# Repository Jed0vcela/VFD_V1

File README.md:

VFD driver for IVL1-8/13 soviet display.
Powered form 5V USB.
SPI interface that can be daisy-chained.
3,3V logic level.
Analog dimming via adjusting anode voltage.
Heater voltage adjustment implemented on board but not tested

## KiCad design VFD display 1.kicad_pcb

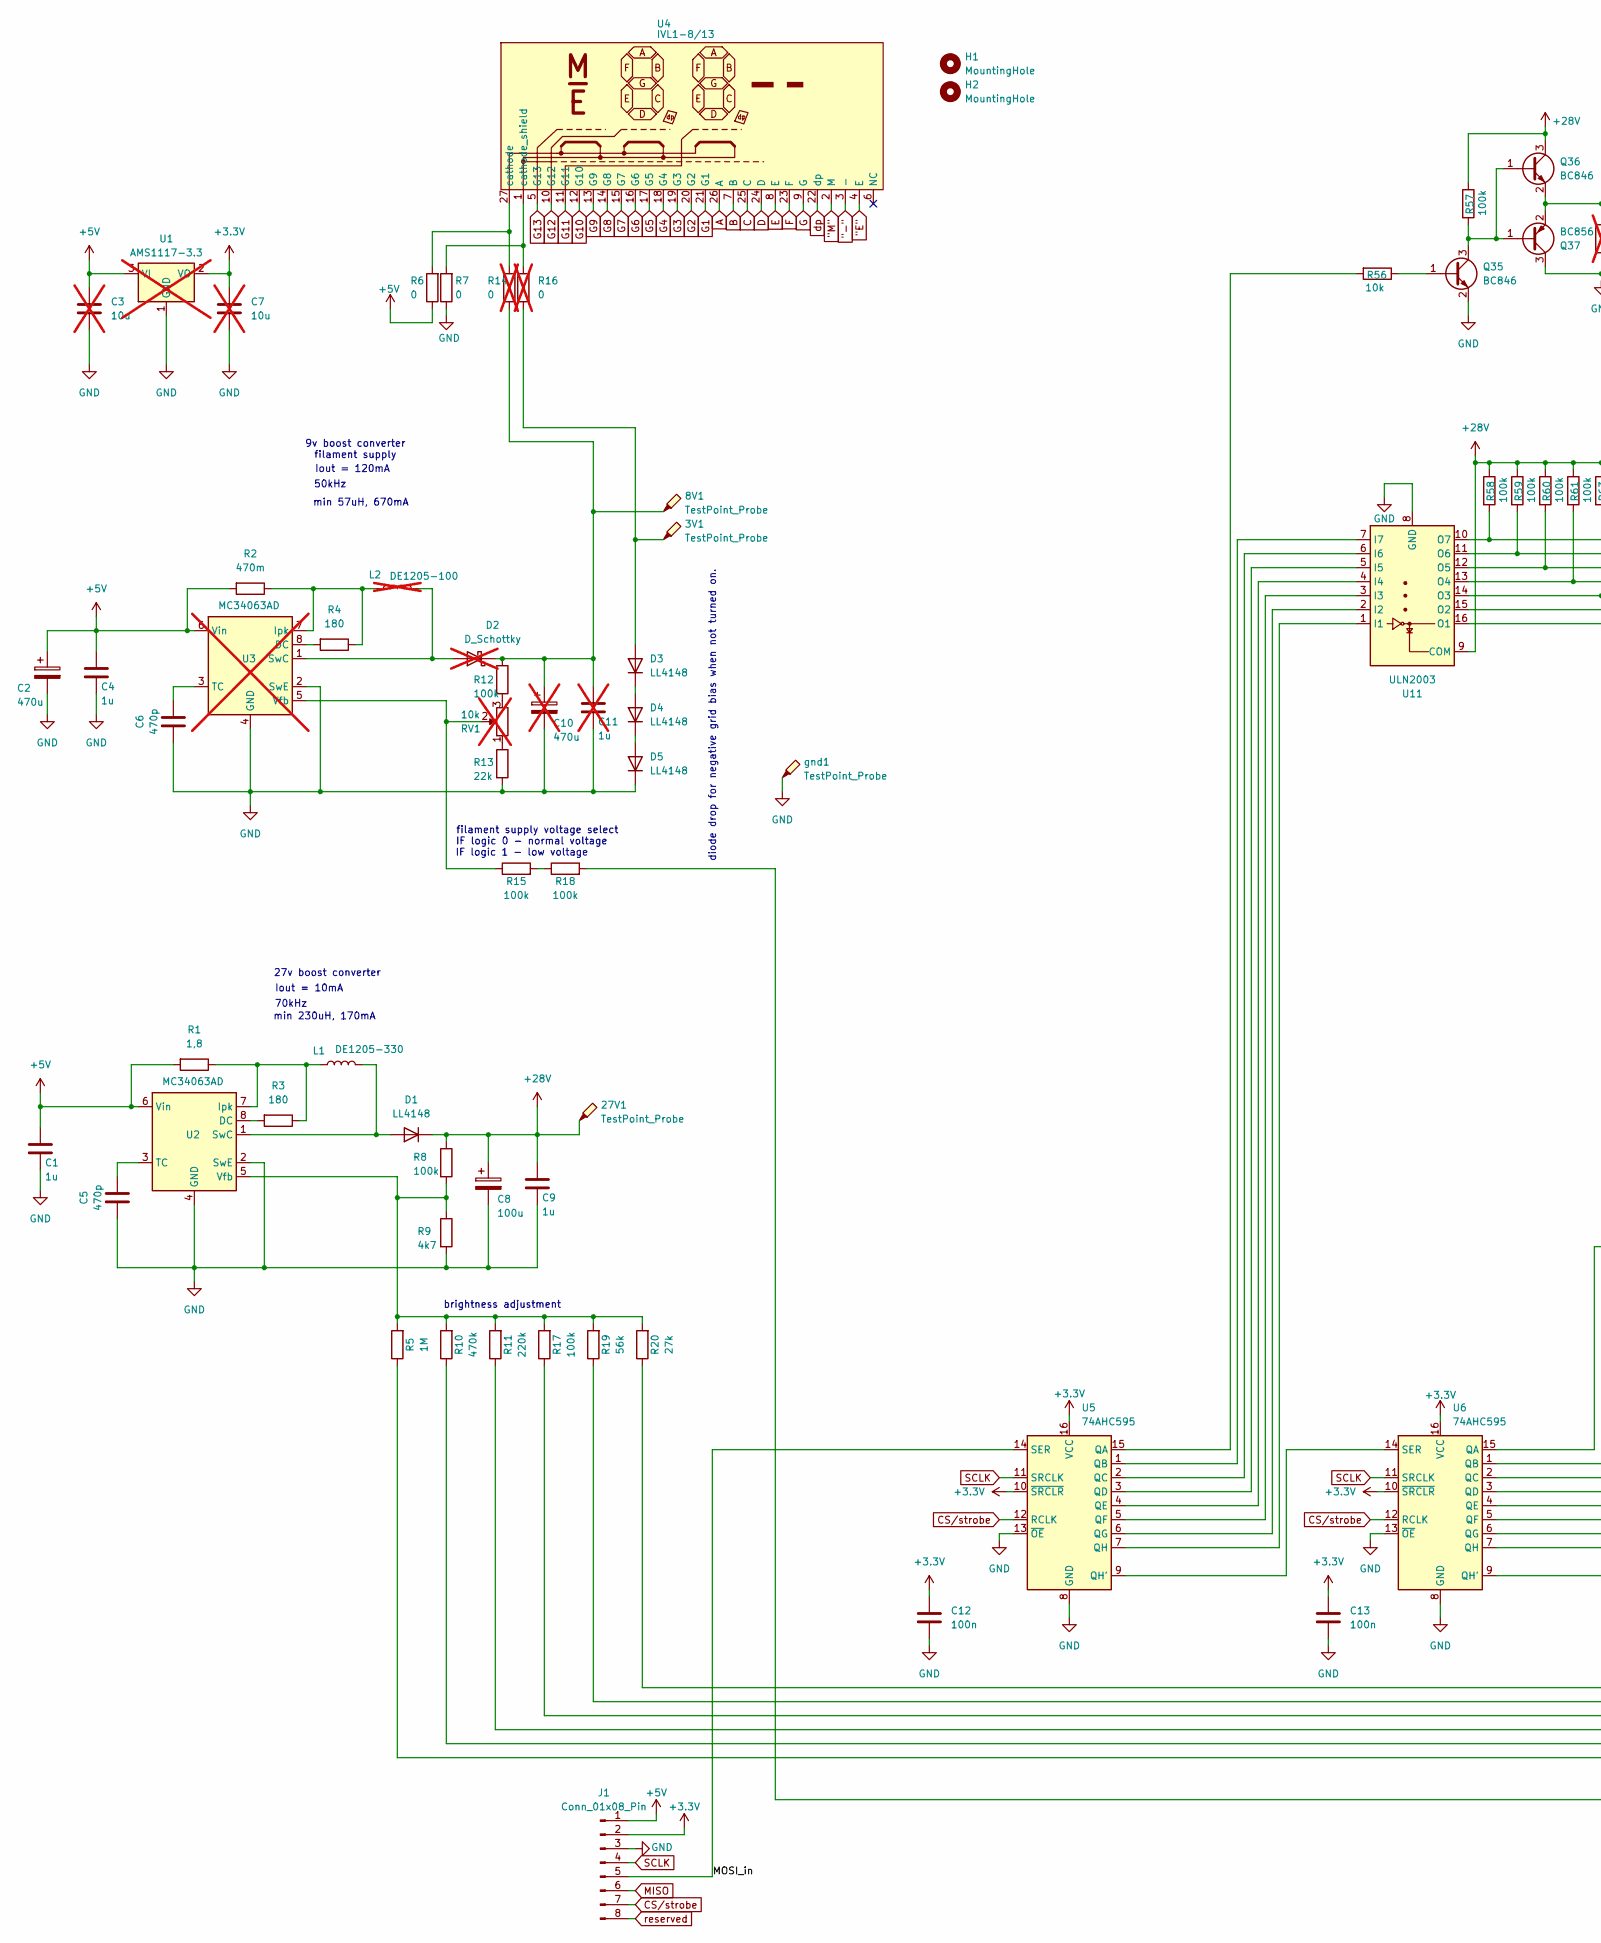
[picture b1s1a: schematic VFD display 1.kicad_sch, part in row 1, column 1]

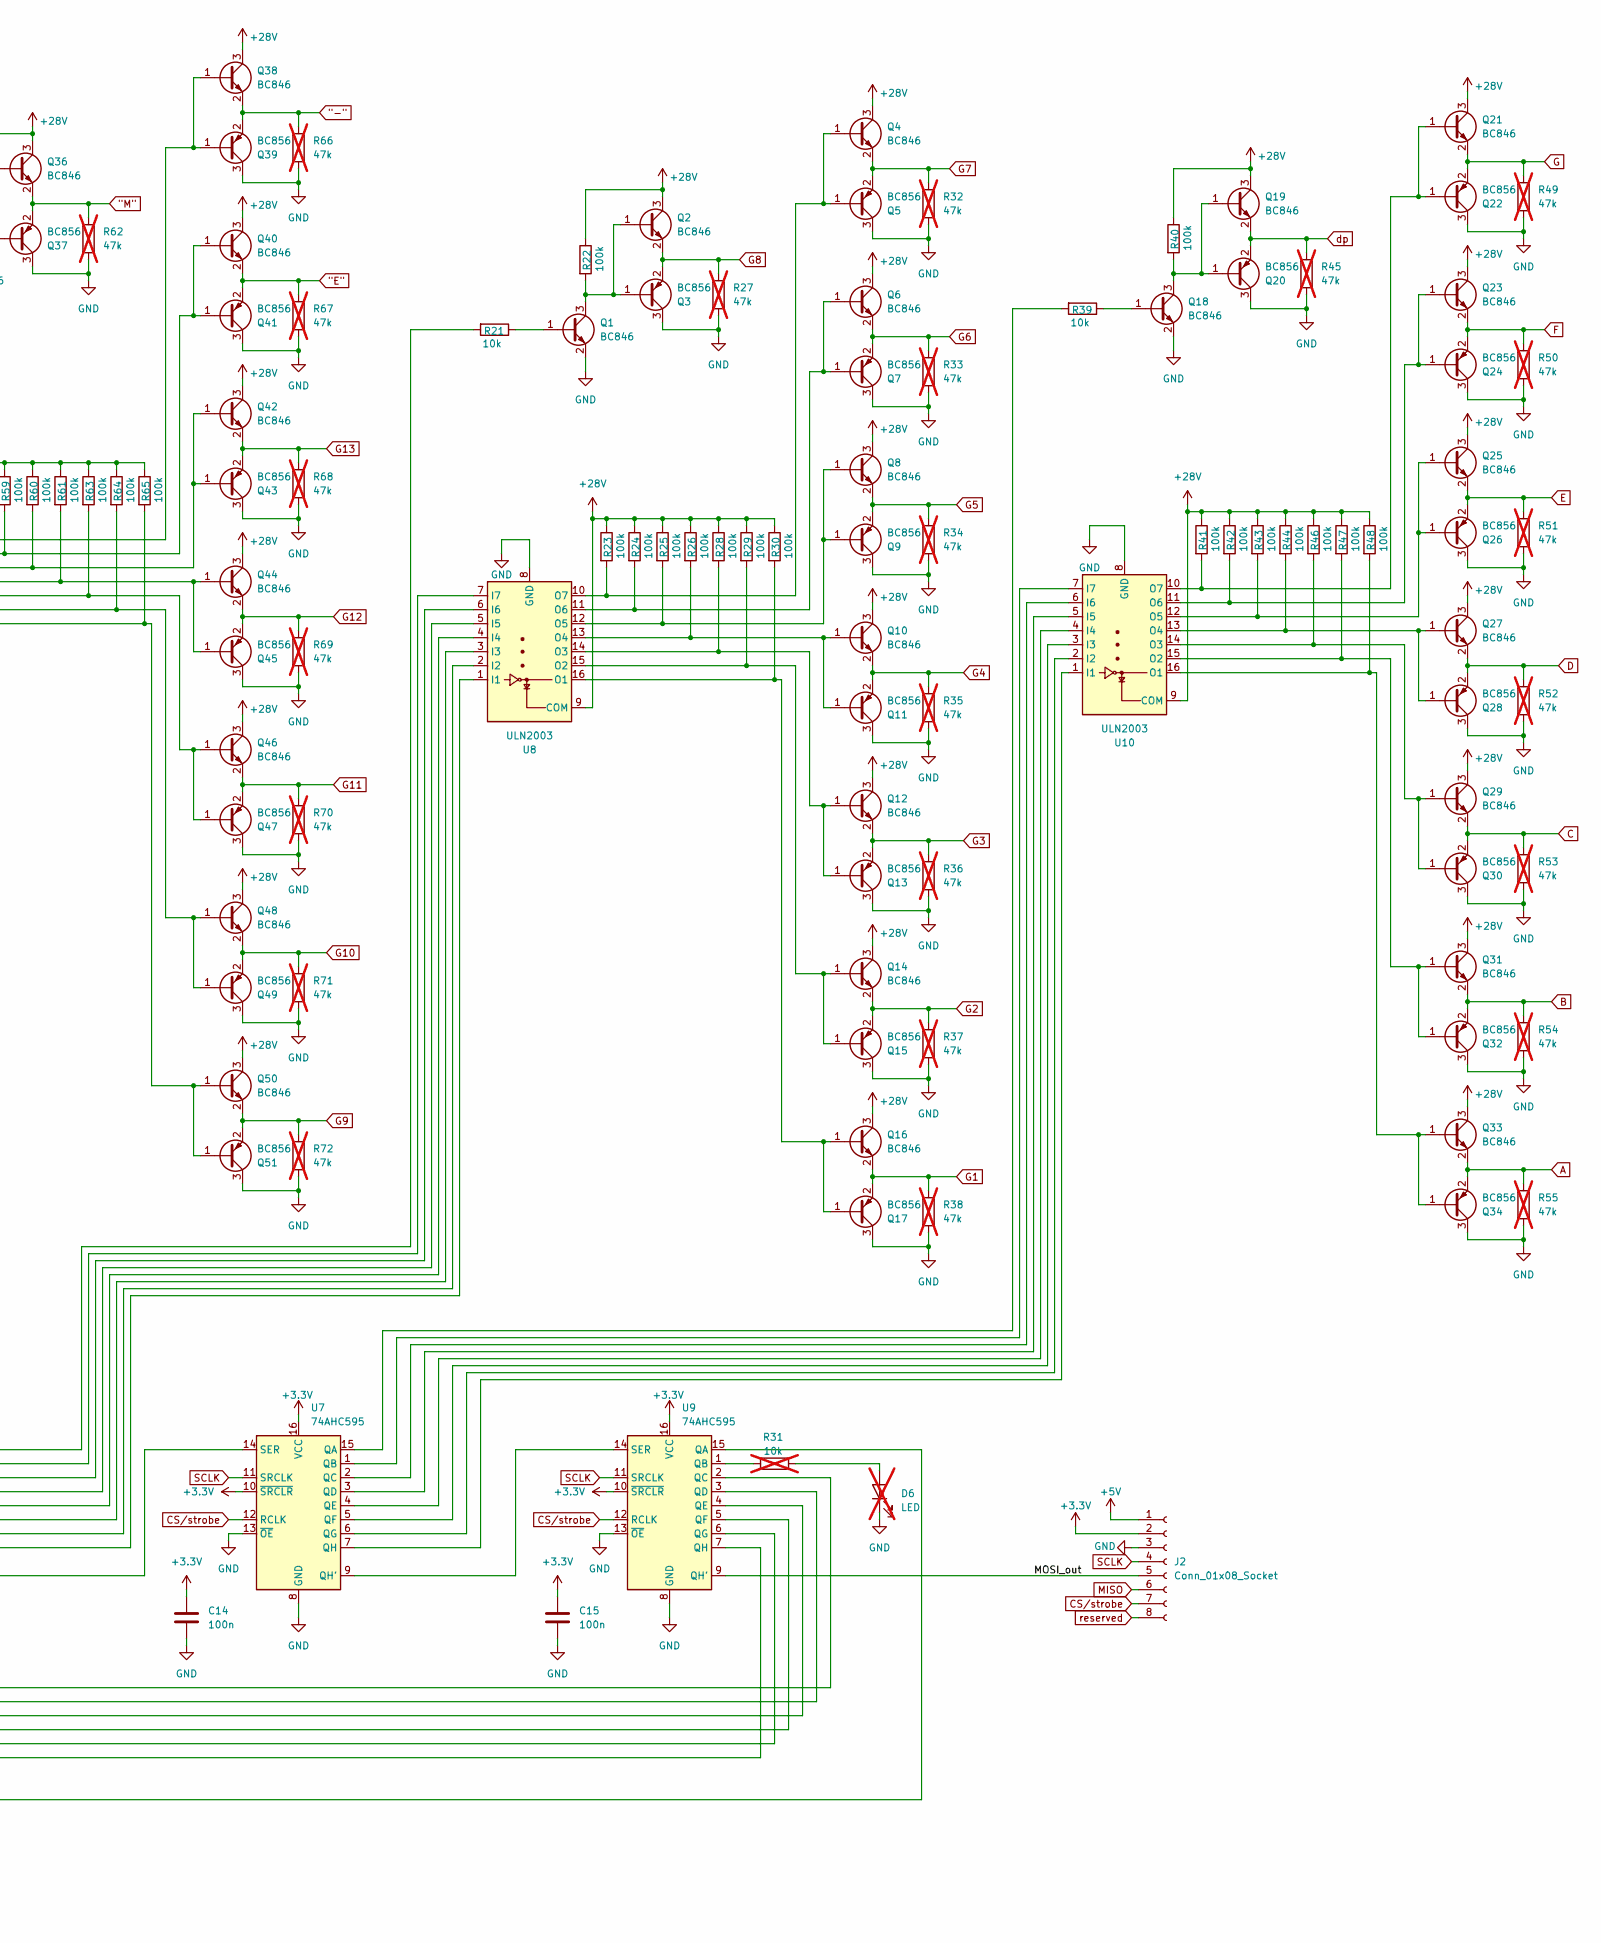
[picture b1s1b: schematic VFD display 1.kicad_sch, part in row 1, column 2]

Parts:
3V1, 8V1, 27V1: TestPoint_Probe; TestPoint_Pad_D1.0mm
C1, C4, C9: 1u; C_1206_3216Metric_Pad1.33x1.80mm_HandSolder
C2: 470u; CP_Radial_D8.0mm_P5.00mm
C3, C7: 10u; C_0805_2012Metric; not fitted
C5, C6: 470p; C_0805_2012Metric
C8: 100u; CP_Radial_D8.0mm_P5.00mm
C10: 470u; CP_Radial_D8.0mm_P5.00mm; not fitted
C11: 1u; C_1206_3216Metric_Pad1.33x1.80mm_HandSolder; not fitted
C12, C13, C14, C15: 100n; C_0805_2012Metric_Pad1.18x1.45mm_HandSolder
D1, D3, D4, D5: LL4148; D_SOD-323_HandSoldering
D2: D_Schottky; D_SMA; not fitted
D6: LED; LED_0805_2012Metric; not fitted
H1, H2: MountingHole; MountingHole_3.2mm_M3_DIN965
J1: Conn_01x08_Pin; PinHeader_1x08_P2.54mm_Horizontal
J2: Conn_01x08_Socket; PinSocket_1x08_P2.54mm_Horizontal
L1: DE1205-330; L_7.3x7.3_H4.5
L2: DE1205-100; L_12x12mm_H6mm; not fitted
Q1, Q2, Q4, Q6, Q8, Q10, Q12, Q14, Q16, Q18, Q19, Q21, Q23, Q25, Q27, Q29, Q31, Q33, Q35, Q36, Q38, Q40, Q42, Q44, Q46, Q48, Q50: BC846; SOT-23
Q3, Q5, Q7, Q9, Q11, Q13, Q15, Q17, Q20, Q22, Q24, Q26, Q28, Q30, Q32, Q34, Q37, Q39, Q41, Q43, Q45, Q47, Q49, Q51: BC856; SOT-23
R1: 1,8; R_0805_2012Metric
R2: 470m; R_0805_2012Metric
R3, R4: 180; R_0805_2012Metric
R5: 1M; R_0805_2012Metric_Pad1.20x1.40mm_HandSolder
R6, R7: 0; R_0805_2012Metric_Pad1.20x1.40mm_HandSolder
R8, R12: 100k; R_0805_2012Metric
R9: 4k7; R_0805_2012Metric
R10: 470k; R_0805_2012Metric_Pad1.20x1.40mm_HandSolder
R11: 220k; R_0805_2012Metric_Pad1.20x1.40mm_HandSolder
R13: 22k; R_0805_2012Metric
R14, R16: 0; R_0805_2012Metric_Pad1.20x1.40mm_HandSolder; not fitted
R15, R17, R18, R22, R23, R24, R25, R26, R28, R29, R30, R40, R41, R42, R43, R44, R46, R47, R48, R57, R58, R59, R60, R61, R63, R64, R65: 100k; R_0805_2012Metric_Pad1.20x1.40mm_HandSolder
R19: 56k; R_0805_2012Metric_Pad1.20x1.40mm_HandSolder
R20: 27k; R_0805_2012Metric_Pad1.20x1.40mm_HandSolder
R21, R39, R56: 10k; R_0805_2012Metric_Pad1.20x1.40mm_HandSolder
R27, R32, R33, R34, R35, R36, R37, R38, R45, R49, R50, R51, R52, R53, R54, R55, R62, R66, R67, R68, R69, R70, R71, R72: 47k; R_0805_2012Metric_Pad1.20x1.40mm_HandSolder; not fitted
R31: 10k; R_0805_2012Metric_Pad1.20x1.40mm_HandSolder; not fitted
RV1: 10k; Potentiometer_Piher_PT-6-V_Vertical_Hole; not fitted
U1: AMS1117-3.3; SOT-223-3_TabPin2; not fitted
U2: MC34063AD; SOIC-8_3.9x4.9mm_P1.27mm
U3: MC34063AD; SOIC-8_3.9x4.9mm_P1.27mm; not fitted
U4: IVL1-8/13; IVL1-813
U5, U6, U7, U9: 74AHC595; SOIC-16_3.9x9.9mm_P1.27mm
U8, U10, U11: ULN2003; SOIC-16_3.9x9.9mm_P1.27mm
gnd1: TestPoint_Probe; TestPoint_Pad_D1.0mm

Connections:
"-": Q38.2 (E), Q39.2 (E), R66.1, U4.3 (-)
"E": Q40.2 (E), Q41.2 (E), R67.1, U4.4 (E)
"M": Q36.2 (E), Q37.2 (E), R62.1, U4.2 (M)
+3.3V: C7.1, C12.1, C13.1, C14.1, C15.1, J1.2, J2.2, U1.2 (VO), U5.10 (~SRCLR), U5.16 (VCC), U6.10 (~SRCLR), U6.16 (VCC), U7.10 (~SRCLR), U7.16 (VCC), U9.10 (~SRCLR), U9.16 (VCC)
+5V: C1.1, C2.1, C3.1, C4.1, J1.1, J2.1, R1.2, R2.2, R6.1, U1.3 (VI), U2.6 (Vin), U3.6 (Vin)
+28V: 27V1.1, C8.1, C9.1, D1.1 (K), Q2.3 (C), Q4.3 (C), Q6.3 (C), Q8.3 (C), Q10.3 (C), Q12.3 (C), Q14.3 (C), Q16.3 (C), Q19.3 (C), Q21.3 (C), Q23.3 (C), Q25.3 (C), Q27.3 (C), Q29.3 (C), Q31.3 (C), Q33.3 (C), Q36.3 (C), Q38.3 (C), Q40.3 (C), Q42.3 (C), Q44.3 (C), Q46.3 (C), Q48.3 (C), Q50.3 (C), R8.1, R22.1, R23.1, R24.1, R25.1, R26.1, R28.1, R29.1, R30.1, R40.1, R41.1, R42.1, R43.1, R44.1, R46.1, R47.1, R48.1, R57.1, R58.1, R59.1, R60.1, R61.1, R63.1, R64.1, R65.1, U8.9 (COM), U10.9 (COM), U11.9 (COM)
/MOSI_in: J1.5, U5.14 (SER)
/MOSI_out: J2.5, U9.9 (QH')
A: Q33.2 (E), Q34.2 (E), R55.1, U4.26 (A)
B: Q31.2 (E), Q32.2 (E), R54.1, U4.7 (B)
C: Q29.2 (E), Q30.2 (E), R53.1, U4.25 (C)
CS/strobe: J1.7, J2.7, U5.12 (RCLK), U6.12 (RCLK), U7.12 (RCLK), U9.12 (RCLK)
D: Q27.2 (E), Q28.2 (E), R52.1, U4.24 (D)
E: Q25.2 (E), Q26.2 (E), R51.1, U4.8 (E)
F: Q23.2 (E), Q24.2 (E), R50.1, U4.23 (F)
G: Q21.2 (E), Q22.2 (E), R49.1, U4.9 (G)
G1: Q16.2 (E), Q17.2 (E), R38.1, U4.21 (G1)
G2: Q14.2 (E), Q15.2 (E), R37.1, U4.20 (G2)
G3: Q12.2 (E), Q13.2 (E), R36.1, U4.19 (G3)
G4: Q10.2 (E), Q11.2 (E), R35.1, U4.18 (G4)
G5: Q8.2 (E), Q9.2 (E), R34.1, U4.17 (G5)
G6: Q6.2 (E), Q7.2 (E), R33.1, U4.16 (G6)
G7: Q4.2 (E), Q5.2 (E), R32.1, U4.15 (G7)
G8: Q2.2 (E), Q3.2 (E), R27.1, U4.14 (G8)
G9: Q50.2 (E), Q51.2 (E), R72.1, U4.13 (G9)
G10: Q48.2 (E), Q49.2 (E), R71.1, U4.12 (G10)
G11: Q46.2 (E), Q47.2 (E), R70.1, U4.11 (G11)
G12: Q44.2 (E), Q45.2 (E), R69.1, U4.10 (G12)
G13: Q42.2 (E), Q43.2 (E), R68.1, U4.5 (G13)
GND: C1.2, C2.2, C3.2, C4.2, C5.1, C6.1, C7.2, C8.2, C9.2, C10.2, C11.2, C12.2, C13.2, C14.2, C15.2, D5.1 (K), D6.1 (K), J1.3, J2.3, Q1.2 (E), Q3.3 (C), Q5.3 (C), Q7.3 (C), Q9.3 (C), Q11.3 (C), Q13.3 (C), Q15.3 (C), Q17.3 (C), Q18.2 (E), Q20.3 (C), Q22.3 (C), Q24.3 (C), Q26.3 (C), Q28.3 (C), Q30.3 (C), Q32.3 (C), Q34.3 (C), Q35.2 (E), Q37.3 (C), Q39.3 (C), Q41.3 (C), Q43.3 (C), Q45.3 (C), Q47.3 (C), Q49.3 (C), Q51.3 (C), R7.1, R9.2, R13.2, R27.2, R32.2, R33.2, R34.2, R35.2, R36.2, R37.2, R38.2, R45.2, R49.2, R50.2, R51.2, R52.2, R53.2, R54.2, R55.2, R62.2, R66.2, R67.2, R68.2, R69.2, R70.2, R71.2, R72.2, U1.1 (GND), U2.2 (SwE), U2.4 (GND), U3.2 (SwE), U3.4 (GND), U5.8 (GND), U5.13 (~OE), U6.8 (GND), U6.13 (~OE), U7.8 (GND), U7.13 (~OE), U8.8 (GND), U9.8 (GND), U9.13 (~OE), U10.8 (GND), U11.8 (GND), gnd1.1
MISO: J1.6, J2.6
unnamed: D1.2 (A), L1.2, U2.1 (SwC)
unnamed: D2.2 (A), L2.2, U3.1 (SwC)
unnamed: 8V1.1, C10.1, C11.1, D2.1 (K), R12.1, R14.1
unnamed: 3V1.1, D3.2 (A), R16.1
unnamed: D3.1 (K), D4.2 (A)
unnamed: D4.1 (K), D5.2 (A)
unnamed: D6.2 (A), R31.2
unnamed: Q1.1 (B), R21.1
unnamed: Q1.3 (C), Q2.1 (B), Q3.1 (B), R22.2
unnamed: Q4.1 (B), Q5.1 (B), R23.2, U8.10 (O7)
unnamed: Q6.1 (B), Q7.1 (B), R24.2, U8.11 (O6)
unnamed: Q8.1 (B), Q9.1 (B), R25.2, U8.12 (O5)
unnamed: Q10.1 (B), Q11.1 (B), R26.2, U8.13 (O4)
unnamed: Q12.1 (B), Q13.1 (B), R28.2, U8.14 (O3)
unnamed: Q14.1 (B), Q15.1 (B), R29.2, U8.15 (O2)
unnamed: Q16.1 (B), Q17.1 (B), R30.2, U8.16 (O1)
unnamed: Q18.1 (B), R39.1
unnamed: Q18.3 (C), Q19.1 (B), Q20.1 (B), R40.2
unnamed: Q21.1 (B), Q22.1 (B), R41.2, U10.10 (O7)
unnamed: Q23.1 (B), Q24.1 (B), R42.2, U10.11 (O6)
unnamed: Q25.1 (B), Q26.1 (B), R43.2, U10.12 (O5)
unnamed: Q27.1 (B), Q28.1 (B), R44.2, U10.13 (O4)
unnamed: Q29.1 (B), Q30.1 (B), R46.2, U10.14 (O3)
unnamed: Q31.1 (B), Q32.1 (B), R47.2, U10.15 (O2)
unnamed: Q33.1 (B), Q34.1 (B), R48.2, U10.16 (O1)
unnamed: Q35.1 (B), R56.1
unnamed: Q35.3 (C), Q36.1 (B), Q37.1 (B), R57.2
unnamed: Q38.1 (B), Q39.1 (B), R58.2, U11.10 (O7)
unnamed: Q40.1 (B), Q41.1 (B), R59.2, U11.11 (O6)
unnamed: Q42.1 (B), Q43.1 (B), R60.2, U11.12 (O5)
unnamed: Q44.1 (B), Q45.1 (B), R61.2, U11.13 (O4)
unnamed: Q46.1 (B), Q47.1 (B), R63.2, U11.14 (O3)
unnamed: Q48.1 (B), Q49.1 (B), R64.2, U11.15 (O2)
unnamed: Q50.1 (B), Q51.1 (B), R65.2, U11.16 (O1)
unnamed: R12.2, RV1.3
unnamed: R13.1, RV1.1
unnamed: R15.2, R18.1
unnamed: R3.2, U2.8 (DC)
unnamed: L1.1, R1.1, R3.1, U2.7 (Ipk)
unnamed: C5.2, U2.3 (TC)
unnamed: R5.2, R8.2, R9.1, R10.2, R11.2, R17.2, R19.2, R20.2, U2.5 (Vfb)
unnamed: R4.2, U3.8 (DC)
unnamed: L2.1, R2.1, R4.1, U3.7 (Ipk)
unnamed: C6.2, U3.3 (TC)
unnamed: R15.1, RV1.2, U3.5 (Vfb)
unnamed: R6.2, R14.2, U4.27 (cathode)
unnamed: R7.2, R16.2, U4.1 (cathode_shield)
unnamed: R56.2, U5.15 (QA)
unnamed: U5.9 (QH'), U6.14 (SER)
unnamed: R21.2, U6.15 (QA)
unnamed: U6.1 (QB), U8.7 (I7)
unnamed: U6.2 (QC), U8.6 (I6)
unnamed: U6.3 (QD), U8.5 (I5)
unnamed: U6.4 (QE), U8.4 (I4)
unnamed: U6.5 (QF), U8.3 (I3)
unnamed: U6.6 (QG), U8.2 (I2)
unnamed: U6.9 (QH'), U7.14 (SER)
unnamed: U6.7 (QH), U8.1 (I1)
unnamed: R39.2, U7.15 (QA)
unnamed: U7.9 (QH'), U9.14 (SER)
unnamed: R18.2, U9.15 (QA)
unnamed: R31.1, U9.1 (QB)
unnamed: R20.1, U9.2 (QC)
unnamed: R19.1, U9.3 (QD)
unnamed: R17.1, U9.4 (QE)
unnamed: R11.1, U9.5 (QF)
unnamed: R10.1, U9.6 (QG)
unnamed: R5.1, U9.7 (QH)
unnamed: U7.7 (QH), U10.1 (I1)
unnamed: U7.6 (QG), U10.2 (I2)
unnamed: U7.5 (QF), U10.3 (I3)
unnamed: U7.4 (QE), U10.4 (I4)
unnamed: U7.3 (QD), U10.5 (I5)
unnamed: U7.2 (QC), U10.6 (I6)
unnamed: U7.1 (QB), U10.7 (I7)
unnamed: U5.7 (QH), U11.1 (I1)
unnamed: U5.6 (QG), U11.2 (I2)
unnamed: U5.5 (QF), U11.3 (I3)
unnamed: U5.4 (QE), U11.4 (I4)
unnamed: U5.3 (QD), U11.5 (I5)
unnamed: U5.2 (QC), U11.6 (I6)
unnamed: U5.1 (QB), U11.7 (I7)
SCLK: J1.4, J2.4, U5.11 (SRCLK), U6.11 (SRCLK), U7.11 (SRCLK), U9.11 (SRCLK)
dp: Q19.2 (E), Q20.2 (E), R45.1, U4.22 (dp)
reserved: J1.8, J2.8

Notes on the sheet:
70kHz
50kHz
min 230uH, 170mA
filament supply voltage select
Iout = 120mA
min 57uH, 670mA
27v boost converter
diode drop for negative grid bias when not turned on.
9v boost converter filament supply
brightness adjustment
IF logic 0 - normal voltage
IF logic 1 - low voltage
Iout = 10mA

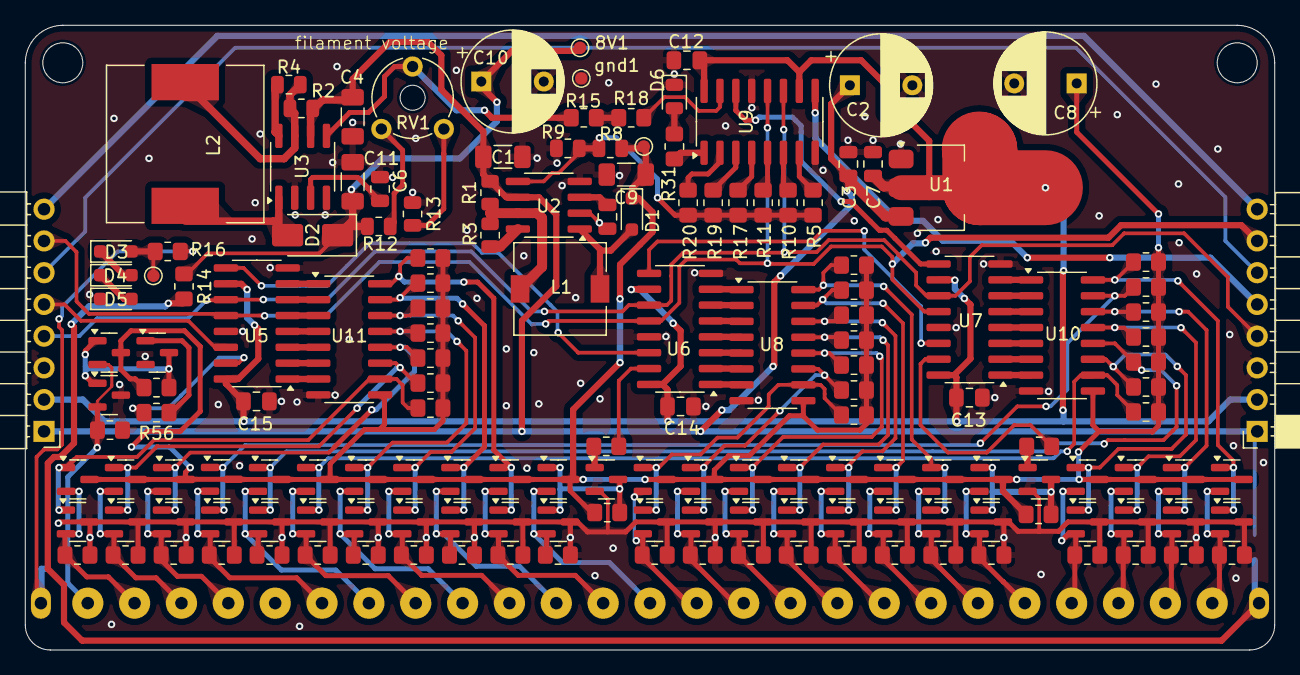
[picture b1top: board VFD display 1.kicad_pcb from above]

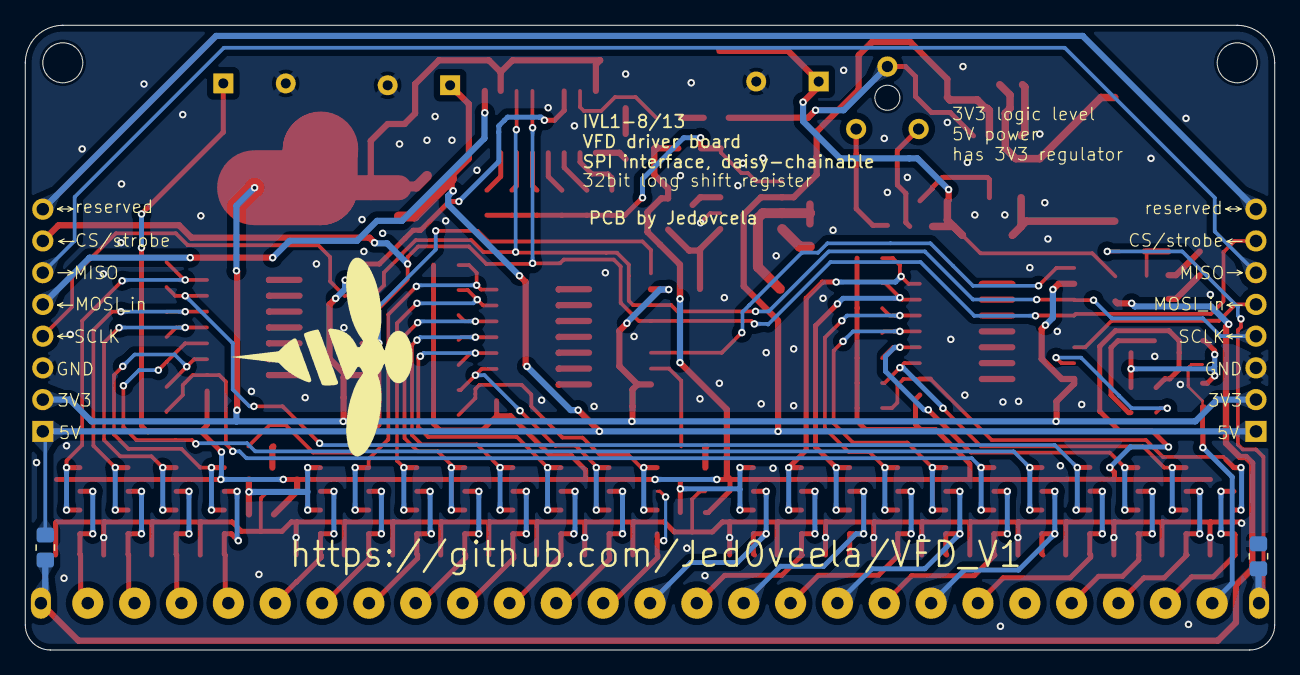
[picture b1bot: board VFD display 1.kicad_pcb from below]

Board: 2 copper layers, 100.0 x 50.0 mm, 166 parts (2 on the bottom side), 116 nets.

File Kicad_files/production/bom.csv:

Designator,Footprint,Quantity,Value,LCSC Part #
"27V1, 3V1, 8V1, GND1",TestPoint_Pad_D1.0mm,4,TestPoint_Probe,
"C1, C4, C9",1206,3,1u,
"C12, C13, C14, C15",0805,4,100n,
C2,CP_Radial_D8.0mm_P5.00mm,1,470u,
"C5, C6",0805,2,470p,
C8,CP_Radial_D8.0mm_P5.00mm,1,100u,
"D1, D3, D4, D5",D_SOD-323_HandSoldering,4,LL4148,
J1,PinHeader_1x08_P2.54mm_Horizontal,1,Conn_01x08_Pin,
J2,PinSocket_1x08_P2.54mm_Horizontal,1,Conn_01x08_Socket,
L1,L_7.3x7.3_H4.5,1,DE1205-330,
"Q1, Q10, Q12, Q14, Q16, Q18, Q19, Q2, Q21, Q23, Q25, Q27, Q29, Q31, Q33, Q35, Q36, Q38, Q4, Q40, Q42, Q44, Q46, Q48, Q50, Q6, Q8",SOT-23,27,BC846,
"Q11, Q13, Q15, Q17, Q20, Q22, Q24, Q26, Q28, Q3, Q30, Q32, Q34, Q37, Q39, Q41, Q43, Q45, Q47, Q49, Q5, Q51, Q7, Q9",SOT-23,24,BC856,
R1,0805,1,"1,8",
R10,0805,1,470k,
R11,0805,1,220k,
"R12, R15, R17, R18, R22, R23, R24, R25, R26, R28, R29, R30, R40, R41, R42, R43, R44, R46, R47, R48, R57, R58, R59, R60, R61, R63, R64, R65, R8",0805,29,100k,
R13,0805,1,22k,
R19,0805,1,56k,
R2,0805,1,470m,
R20,0805,1,27k,
"R21, R39, R56",0805,3,10k,
"R3, R4",0805,2,180,
R5,0805,1,1M,
"R6, R7",0805,2,0,
R9,0805,1,4k7,
"U10, U11, U8",SOIC-16_3.9x9.9mm_P1.27mm,3,ULN2003,
U2,SOIC-8_3.9x4.9mm_P1.27mm,1,MC34063AD,
U4,IVL1-813,1,IVL1-8/13,
"U5, U6, U7, U9",SOIC-16_3.9x9.9mm_P1.27mm,4,74AHC595,

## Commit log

2025-11-04 upload
2025-11-04 silkscreen and production files
2026-01-22 dir reupload
2026-01-22 Add README with VFD driver details
2026-01-22 Add blank line for improved readability in README
2026-01-22 Update README with dimming and heater adjustment details
    Added information about analog dimming and heater voltage adjustment.
2026-01-22 Add images to README for better visualization
